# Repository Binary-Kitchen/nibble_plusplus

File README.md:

# Nibble++
A simple PCB to test your SMD hand-soldering skills. Going down to sand grain sized 01005 SMD parts, this button is a challenge for experienced "soldiers" and those who want to become one.

## Bill of Material
| Designator |       Package      | Quantity |   Designation   |
|:----------:|:------------------:|----------|:---------------:|
| BT1        | SMD Battery Holder | 1        | CR2023          |
| C1         | 0805 SMD Capacitor | 1        | 100n F          |
| C2         | 0805 SMD Capacitor | 1        | 1µ F            |
| C3         | 0805 SMD Capacitor | 1        | 100n F          |
| D1         | 0805 SMD LED       | 1        | LED Red         |
| D2         | 0603 SMD LED       | 1        | LED Orange      |
| D3         | 0402 SMD LED       | 1        | LED Yellow      |
| D4         | 0201 SMD LED       | 1        | LED Green       |
| D5         | 0201 SMD LED       | 1        | LED Blue        |
| R1         | 0805 SMD Resistor  | 1        |  82 Ohm         |
| R2         | 0603 SMD Resistor  | 1        |  82 Ohm         |
| R3         | 0402  SMD Resistor | 1        |  62 Ohm         |
| R4         | 0201 SMD Resistor  | 1        | 330 Ohm         |
| R5         | 01005 SMD Resistor | 1        |  33 Ohm         |
| R6,R7      | 0805 SMD Resistor  | 2        | 100k Ohm        |
| SW1        | SMD Switch         | 1        |                 |
| U1         | SOIC-8 NE555       | 1        |                 |
| U2         | SOP-16 CD4017      | 1        |                 |

## Manual
TBD

## Idea
The Idea origins to Ken Olsen and his Attiny SMD Challenge. Many thanks to Ken Olsen for the idea and for opening up this great work to creative commons.

## Name
The name Nibble++ origins from a simple [nibble peg](https://github.com/Binary-Kitchen/SolderingTutorial/tree/master/NibblePegDIP) which has been developed one year earlier. A Nibble is a unit for the amount of 4 bits (https://en.wikipedia.org/wiki/Nibble). Because we are using five LEDs we incremented the value ;).

## Copyright and Authorship
- Idea: [CC-BY-SA 3.0](https://creativecommons.org/licenses/by-sa/3.0/) - [Ken Olsen (www.MakersBox.us)](https://github.com/aspro648/KiCad/tree/master/projects/Attiny/Attiny85Challenge)
- PCB-Layout: [CC-BY-SA 3.0](https://creativecommons.org/licenses/by-sa/3.0/) - [Ken Olsen](http://www.MakersBox.us), [Thomas Schmid and Timo Schindler](https://www.binary-kitchen.de)
- Manual (TeX): [LPPL](https://www.latex-project.org/lppl.txt) - [Marei Peischl](https://peitex.de)
- Manual (pdf): [CC-BY-SA 4.0](https://creativecommons.org/licenses/by-sa/4.0/) - [Binary Kitchen e.V.](https://www.binary-kitchen.de)

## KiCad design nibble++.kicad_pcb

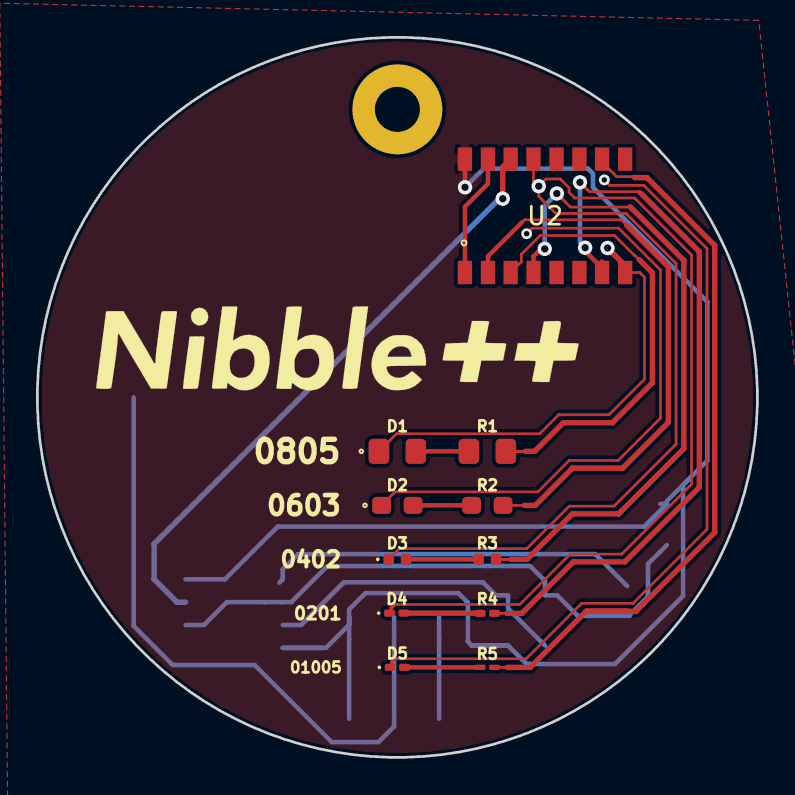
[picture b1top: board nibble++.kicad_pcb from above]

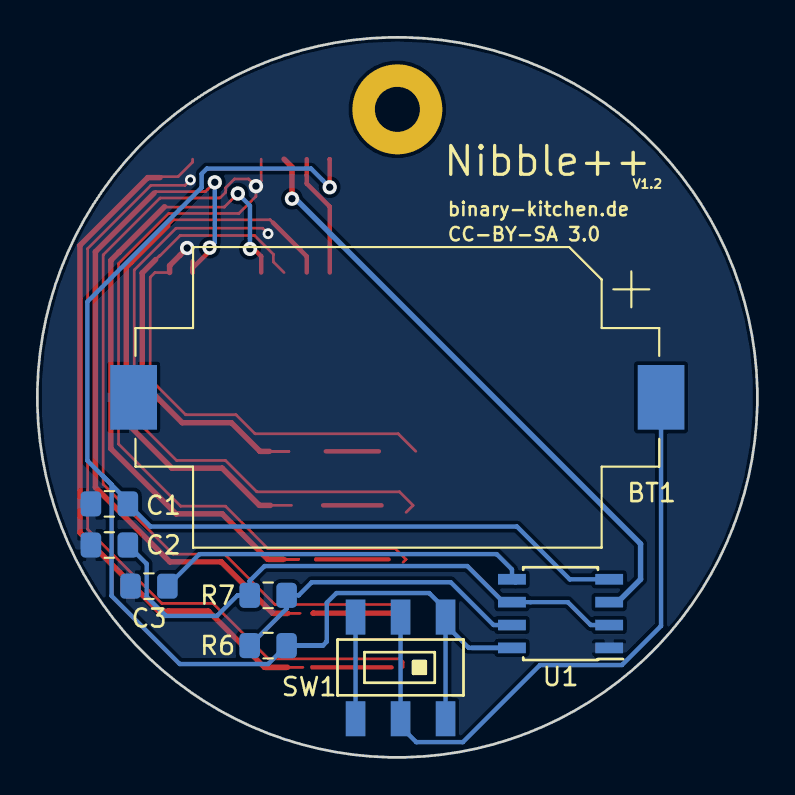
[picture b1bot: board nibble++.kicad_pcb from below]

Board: 2 copper layers, 40.0 x 40.0 mm, 19 parts (8 on the bottom side), 18 nets.

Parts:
BT1: CR2023; BatteryHolder_Keystone_1060_1x2032
C1: 100n; C_0805_2012Metric_Pad1.15x1.40mm_HandSolder
C2: 1µ F; C_0805_2012Metric_Pad1.15x1.40mm_HandSolder
C3: 100n F; C_0805_2012Metric_Pad1.15x1.40mm_HandSolder
D1: 0805 LED Red; LED_0805_2012Metric_Pad1.15x1.40mm_HandSolder_simple_drawing
D2: 0603 LED Orange; LED_0603_1608Metric_Pad1.05x0.95mm_HandSolder_simple_drawing
D3: 0402 LED Yellow; LED_0402_1005Metric
D4: 0201 LED Green; LED_0201_0603Metric_hand_soldering
D5: 0201 LED Blue; LED_0201_0603Metric_hand_soldering
R1: 100 Ohm; R_0805_2012Metric_Pad1.15x1.40mm_HandSolder
R2: 100 Ohm; R_0603_1608Metric_Pad1.05x0.95mm_HandSolder
R3: 100 Ohm; R_0402_1005Metric
R4: 150 Ohm; R_0201_0603Metric_hand_soldering
R5: 200 Ohm; R_01005_0402Metric_hand_soldering
R6, R7: 100k Ohm; R_0805_2012Metric_Pad1.15x1.40mm_HandSolder
SW1: SW_DPDT_x2; smd_switch_slide
U1: NE555; SOIC-8_3.9x4.9mm_P1.27mm
U2: 4017; SOP-16_4.4x10.4mm_P1.27mm_simple_drawing

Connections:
+3V3: BT1.1, SW1.2
GND: BT1.2, C1.1, C2.1, C3.2, D1.1, D2.1, D3.1, D4.1, D5.1, U1.1, U2.8, U2.13
unnamed: C2.2, R7.2, U1.2, U1.6
unnamed: C3.1, U1.5
unnamed: D1.2, R1.1
unnamed: D2.2, R2.1
unnamed: D3.2, R3.1
unnamed: D4.2, R4.1
unnamed: D5.2, R5.1
unnamed: R1.2, U2.3
unnamed: R2.2, U2.2
unnamed: R3.2, U2.4
unnamed: R4.2, U2.7
unnamed: R5.2, U2.10
unnamed: R6.2, R7.1, U1.7
unnamed: U1.3, U2.14
unnamed: U2.1, U2.15
VS: C1.2, R6.1, SW1.1, U1.4, U1.8, U2.16

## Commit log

2018-11-10 added simple .gitignore
2018-11-10 inital commit
2018-11-10 Update .gitignore and apply changes to the repo
2018-11-10 managed to layout without visible via
2018-11-11 update component values for ne555 oscillator
    Frequency is now 4.8 Hz
2018-11-11 cleanup schematic and add title
2018-11-11 added custom footprints for smd 0201 and 01005 for hand-soldering
2018-11-11 changed some footprints and made the surface printing nicer
2018-11-11 added line in front mask layer
2018-11-11 remove some silkscreen lines
2018-11-11 finish design of nibble++ :)
2018-11-12 Changed track-layout slightly for better soldering
2018-11-12 added readme and some pictures
2018-11-12 added file with used licences
2018-11-12 removed back.png from readme
2018-11-12 add 3d model of on-off-switch
2018-11-12 fix typo
2018-11-12 add logo to site layout and update description
2018-11-12 remove some silkscreen features and cleanup layout
2018-11-12 Renamed project to nibble++
2018-11-12 fixed overlaying routes
2018-11-13 added additional information for some parts
2018-11-13 generated simple BOM
2018-11-13 updated README.md with BOM
2018-12-18 fixed too small labelling and some lines
2019-01-07 adjusted thickness of drawing
2019-01-07 Change routing on the visible tracks
2019-01-07 bump version number
2019-01-07 add gerber files
2019-04-19 fixed some errors
2019-04-28 add LED orientation on PCB image
2019-07-09 modified resistor value. fixing #3
2021-04-20 replaced gerber files
2021-04-20 fixed #4
2021-04-20 added zip
